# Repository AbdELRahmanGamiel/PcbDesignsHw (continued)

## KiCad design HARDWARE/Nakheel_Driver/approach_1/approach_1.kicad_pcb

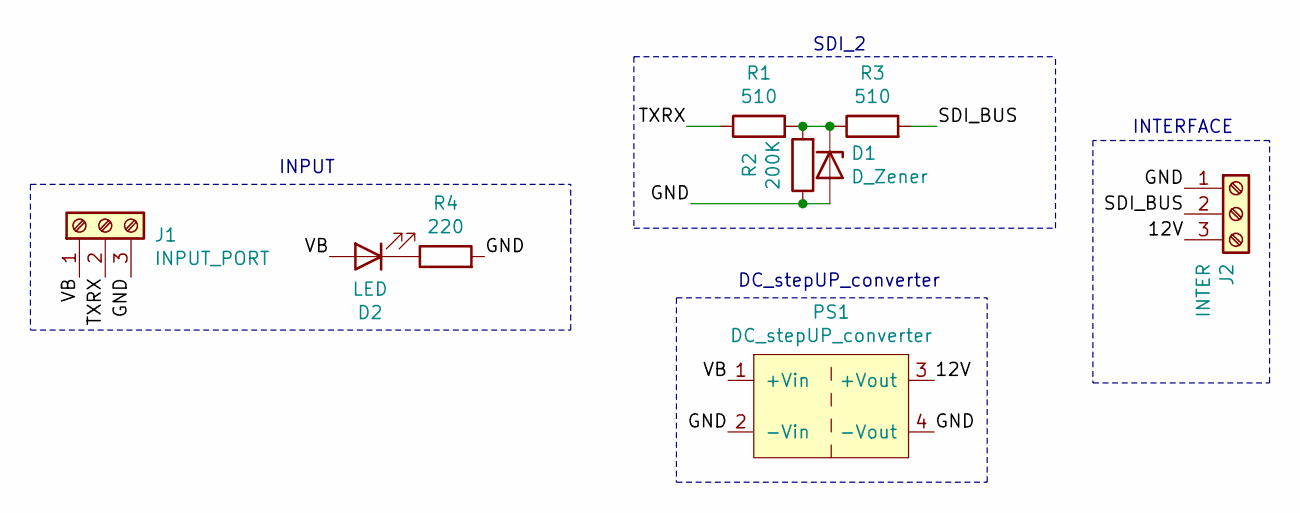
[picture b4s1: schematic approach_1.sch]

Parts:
D1: D_Zener; D_A-405_P7.62mm_Horizontal
D2: LED; LED_D5.0mm
J1: INPUT_PORT; PhoenixContact_MSTBA_2,5_3-G-5,08_1x03_P5.08mm_Horizontal
J2: INTER; PhoenixContact_MSTBA_2,5_3-G-5,08_1x03_P5.08mm_Horizontal
PS1: DC_stepUP_converter
R1, R3: 510; R_Axial_DIN0207_L6.3mm_D2.5mm_P10.16mm_Horizontal
R2: 200K; R_Axial_DIN0207_L6.3mm_D2.5mm_P10.16mm_Horizontal
R4: 220; R_Axial_DIN0207_L6.3mm_D2.5mm_P10.16mm_Horizontal

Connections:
/12V: J2.3, PS1.3 (+Vout)
/GND: D1.2 (A), J1.3, J2.1, PS1.2 (-Vin), PS1.4 (-Vout), R2.1, R4.2
/SDI_BUS: J2.2, R3.2
/TXRX: J1.2, R1.1
/VB: D2.2 (A), J1.1, PS1.1 (+Vin)
unnamed: D1.1 (K), R1.2, R2.2, R3.1
unnamed: D2.1 (K), R4.1

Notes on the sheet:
INPUT
DC_stepUP_converter
SDI_2
INTERFACE

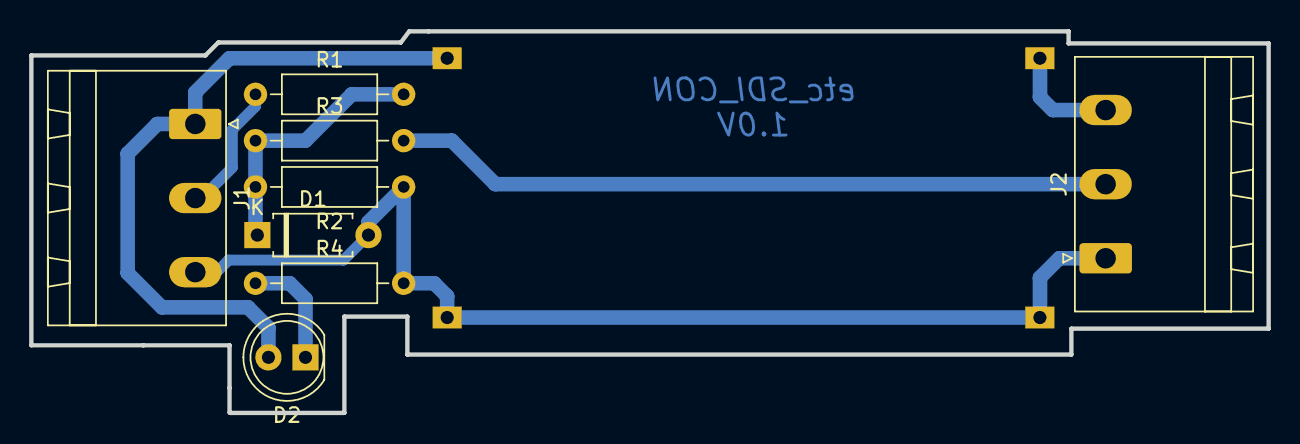
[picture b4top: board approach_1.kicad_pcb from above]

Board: 2 copper layers, 84.8 x 26.2 mm, 9 parts (0 on the bottom side), 7 nets.

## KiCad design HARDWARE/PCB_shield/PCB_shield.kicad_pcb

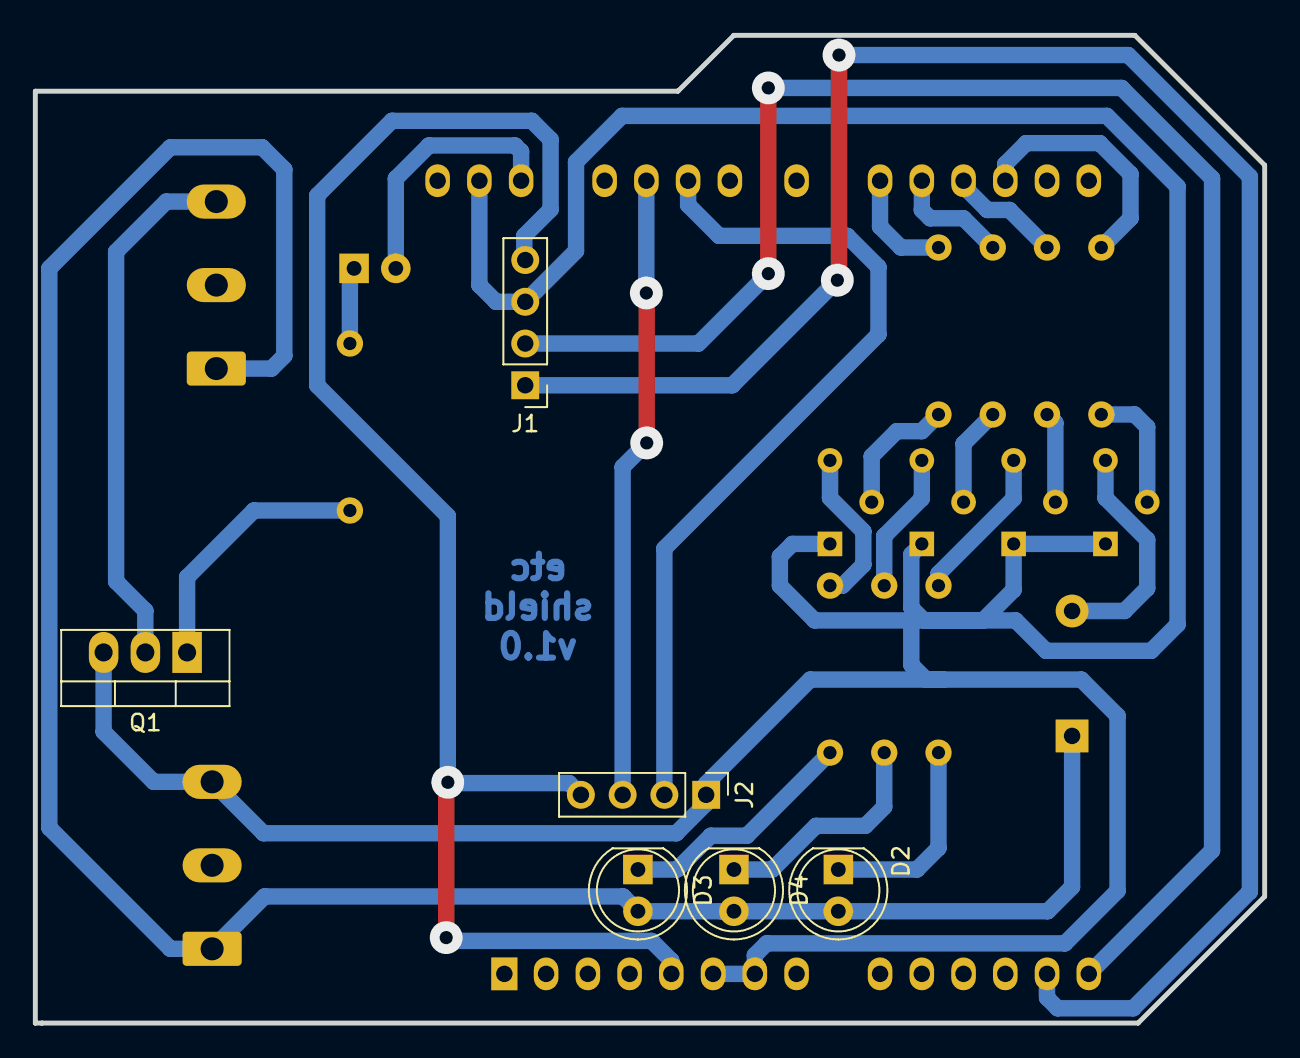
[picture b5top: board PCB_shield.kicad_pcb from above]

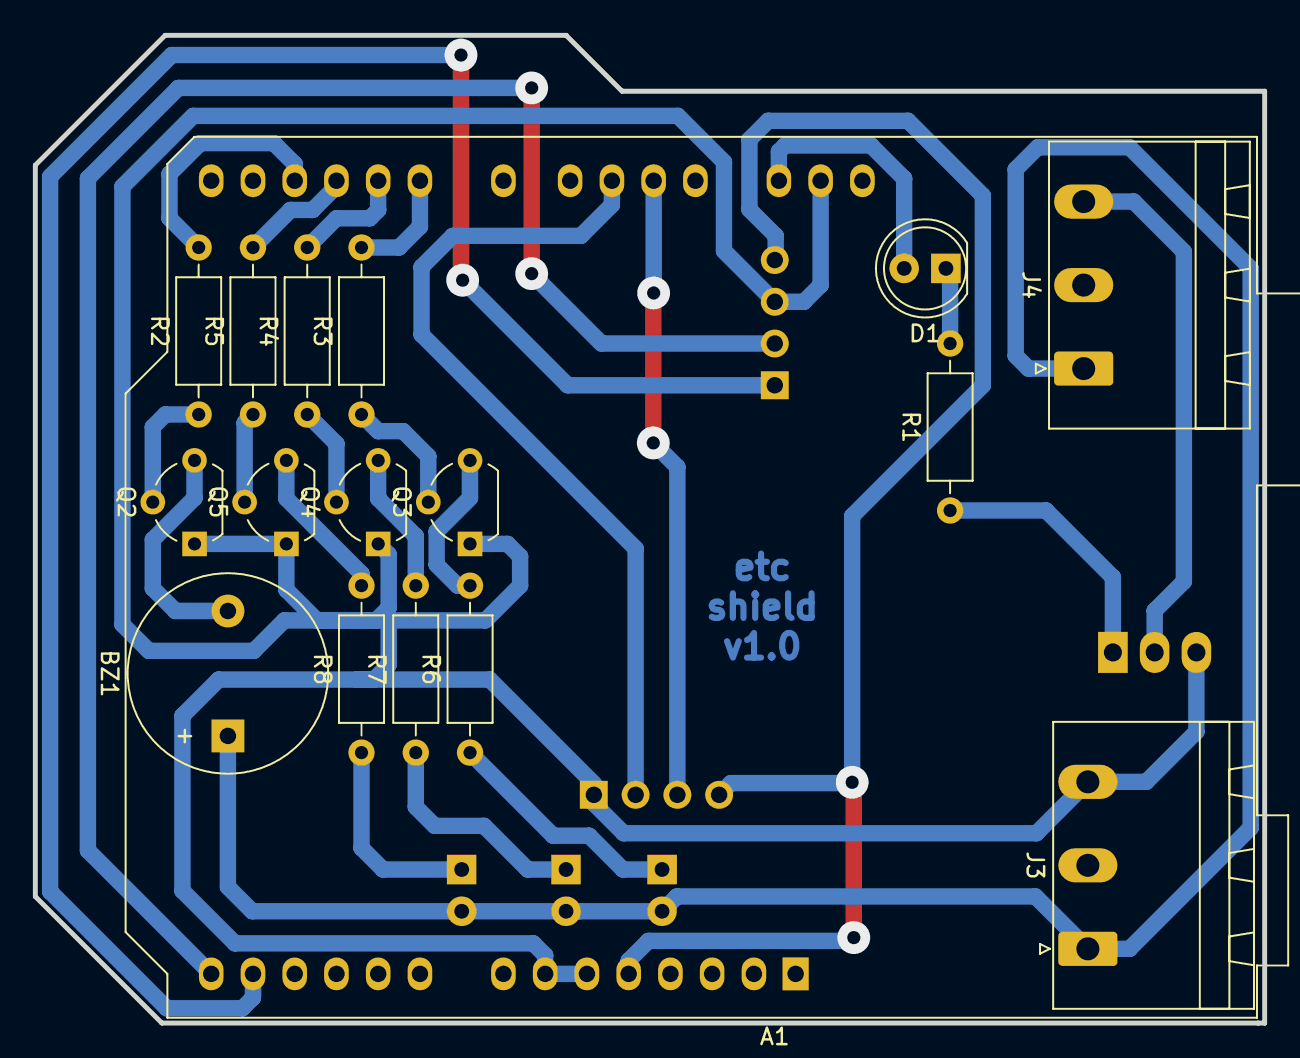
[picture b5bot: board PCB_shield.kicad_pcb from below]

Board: 2 copper layers, 74.8 x 60.1 mm, 23 parts (17 on the bottom side), 26 nets.

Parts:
A1: Arduino_UNO_R2
BZ1: Buzzer; Buzzer_12x9.5RM7.6
D1, D4: Red; LED_D5.0mm
D2: Blue; LED_D5.0mm
D3: Green; LED_D5.0mm
J1: MLX; PinHeader_1x04_P2.54mm_Vertical
J2: Ultra_sonic; PinHeader_1x04_P2.54mm_Vertical
J3, J4: pump; PhoenixContact_MSTBA_2,5_3-G-5,08_1x03_P5.08mm_Horizontal
Q1: TIP41C; TO-220-3_Vertical
Q2, Q3, Q4, Q5: 2N2219; TO-92L_Wide
R1, R2, R3, R4, R5: 1K; R_Axial_DIN0207_L6.3mm_D2.5mm_P10.16mm_Horizontal
R6, R7, R8: 470; R_Axial_DIN0207_L6.3mm_D2.5mm_P10.16mm_Horizontal

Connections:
/5V: A1.5, J1.4, J2.4
/12V: BZ1.1, D2.2, D3.2, D4.2, J3.1, J4.1
/BLUE: A1.18, R5.2
/BUZZER: A1.17, R2.2
/ECHO: A1.24, J2.2
/GND: A1.6, A1.7, A1.29, J1.3, J2.1, J3.3, Q1.3, Q2.1, Q3.1, Q4.1, Q5.1
/GREEN: A1.20, R3.2
/OUTPUT: J4.3, Q1.2
/RED: A1.19, R4.2
/SCL: A1.14, J1.2
/SDA: A1.13, J1.1
/TRIG: A1.25, J2.3
/pump: A1.28, D1.2
unnamed: BZ1.2, Q2.3
unnamed: D1.1, R1.2
unnamed: D2.1, R8.1
unnamed: D3.1, R6.1
unnamed: D4.1, R7.1
unnamed: Q1.1, R1.1
unnamed: Q2.2, R2.1
unnamed: Q3.2, R3.1
unnamed: Q3.3, R6.2
unnamed: Q4.2, R4.1
unnamed: Q4.3, R7.2
unnamed: Q5.2, R5.1
unnamed: Q5.3, R8.2

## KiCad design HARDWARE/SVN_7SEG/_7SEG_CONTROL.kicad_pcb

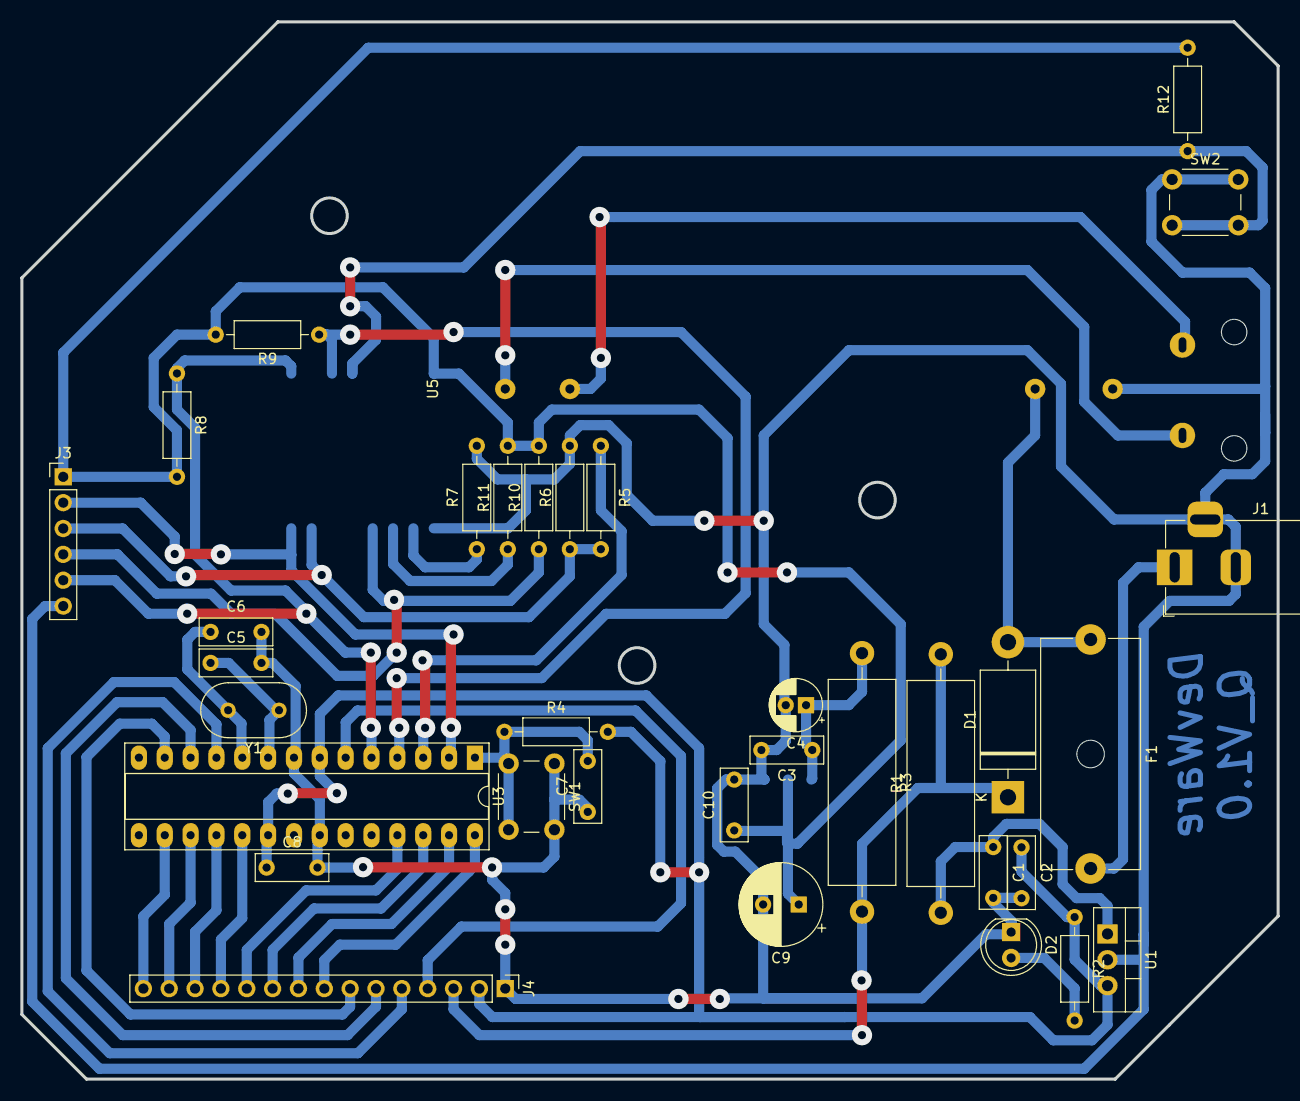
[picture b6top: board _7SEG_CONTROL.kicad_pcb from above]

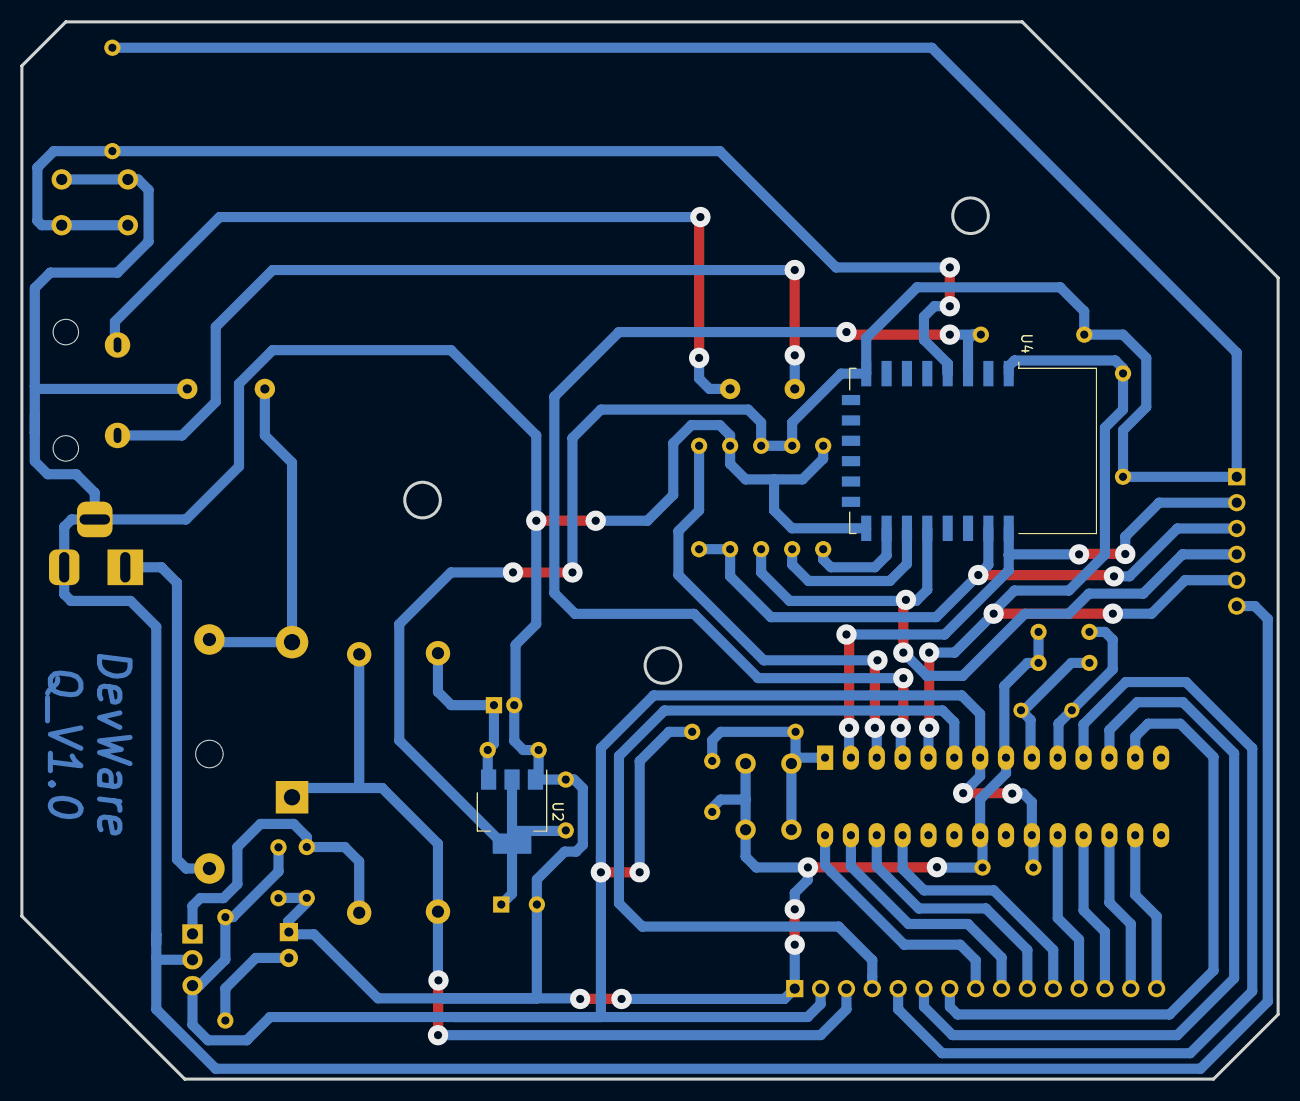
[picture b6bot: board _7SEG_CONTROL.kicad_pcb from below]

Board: 2 copper layers, 123.4 x 103.9 mm, 37 parts (2 on the bottom side), 35 nets.

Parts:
C1, C3: 334; C_Disc_D7.0mm_W2.5mm_P5.00mm
C2, C7, C10: 104; C_Disc_D7.0mm_W2.5mm_P5.00mm
C4: 10UF; CP_Radial_D5.0mm_P2.00mm
C5, C6: 22P; C_Disc_D7.0mm_W2.5mm_P5.00mm
C8: 0.1UF; C_Disc_D7.0mm_W2.5mm_P5.00mm
C9: 100UF; CP_Radial_D8.0mm_P3.50mm
D1: 1N5407; D_DO-201AD_P15.24mm_Horizontal
D2: LED; LED_D5.0mm
F1: Fuse; Fuseholder_Cylinder-5x20mm_Schurter_0031_8201_Horizontal_Op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
J1: Barrel_Jack_Switch; BarrelJack_Horizontal
J2: AC_Socket
J3: CONFIG_ESP12; PinHeader_1x06_P2.54mm_Vertical
J4: Display_Board; PinHeader_1x15_P2.54mm_Vertical
R1: 10/2W; R_Axial_Power_L20.0mm_W6.4mm_P25.40mm
R2: 330; R_Axial_DIN0207_L6.3mm_D2.5mm_P10.16mm_Horizontal
R3: 10/3W; R_Axial_Power_L20.0mm_W6.4mm_P25.40mm
R4, R5, R6, R12: 10K; R_Axial_DIN0207_L6.3mm_D2.5mm_P10.16mm_Horizontal
R7, R8, R9, R10, R11: 12K; R_Axial_DIN0207_L6.3mm_D2.5mm_P10.16mm_Horizontal
SW1, SW2: SW_Push; SW_PUSH_6mm_H7.3mm
U1: L7805; TO-220-3_Vertical
U2: AMS1117-3.3; SOT-223-3_TabPin2
U3: ATmega328-PU; DIP-28_W7.62mm_Socket_LongPads
U4: ESP-12E
U5: PS-12VDC; PS_12VDC
Y1: 16MH; Resonator-2Pin_W10.0mm_H5.0mm

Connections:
/3.3V: C9.1, C10.1, J3.1, R8.2, R9.2, R10.2, R11.2, R12.2, U2.2, U4.8
/5V: C2.1, C8.1, J4.2, R2.1, R4.2, U1.3, U3.7, U3.20
/12V: D1.1, J4.3, R1.2, R3.2
/A_D1: J4.15, U3.16
/A_D2: J4.11, U3.25
/A_D3: J4.7, U3.13
/B_D1: J4.12, U3.19
/B_D2: J4.8, U3.28
/B_D3: J4.4, U3.6
/C_D1: J4.13, U3.18
/C_D2: J4.9, U3.27
/C_D3: J4.5, U3.11
/D_D1: J4.14, U3.17
/D_D2: J4.10, U3.26
/D_D3: J4.6, U3.12
/EN: R9.1, U3.4, U4.3
/GND: C1.2, C2.2, C3.2, C4.2, C5.2, C6.2, C7.1, C8.2, C9.2, C10.2, D2.1, J1.2, J1.3, J3.6, J4.1, R6.2, R7.2, SW1.1, SW2.1, U1.2, U2.1, U3.8, U3.22, U4.15, U5.4
/IO0: J3.4, R10.1, U4.18
/IO2: R11.1, U4.17
/IO15: R7.1, U4.16
/Interrupt: R12.1, SW2.2, U4.4
/RST: J3.5, R8.1, U3.5, U4.1
/RX-MCU: J3.2, U3.2, U4.22
/RXD: J3.3, R5.2, R6.1, U4.21
/TX_MCU: R5.1, U3.3
/V+: D1.2, F1.1, U5.3
unnamed: C1.1, R1.1, U1.1
unnamed: C3.1, C4.1, R3.1, U2.3
unnamed: C5.1, U3.9, Y1.1
unnamed: C6.1, U3.10, Y1.2
unnamed: C7.2, R4.1, SW1.2, U3.1
unnamed: D2.2, R2.2
unnamed: F1.2, J1.1
unnamed: J2.L, U5.1
unnamed: J2.N, U5.2

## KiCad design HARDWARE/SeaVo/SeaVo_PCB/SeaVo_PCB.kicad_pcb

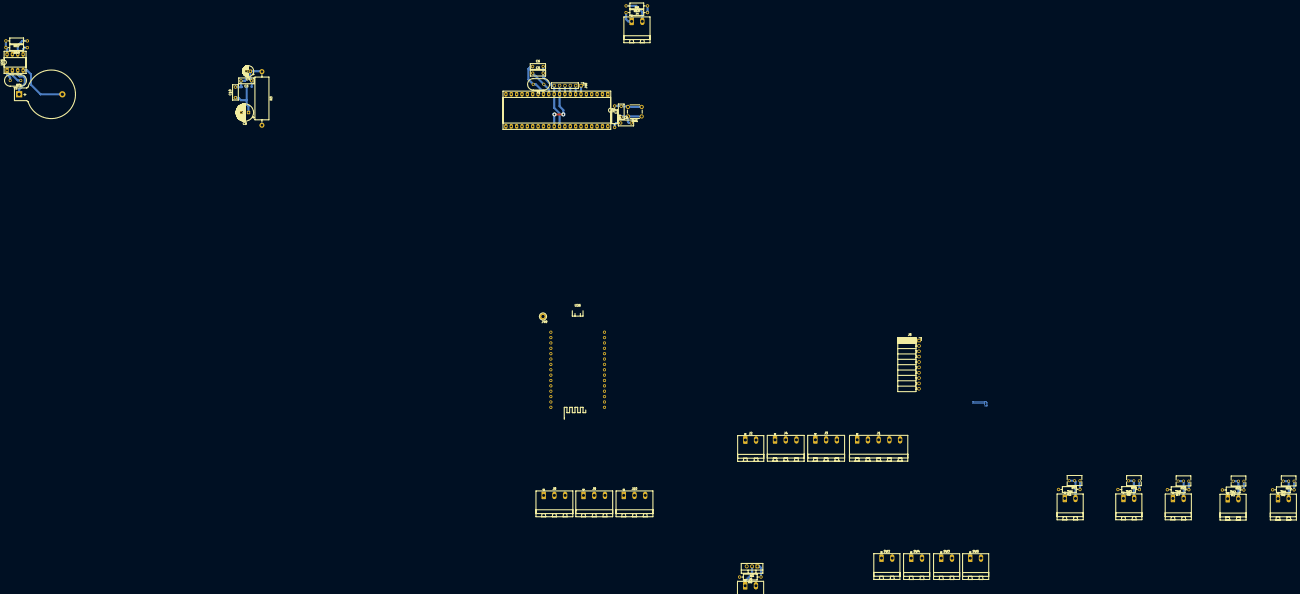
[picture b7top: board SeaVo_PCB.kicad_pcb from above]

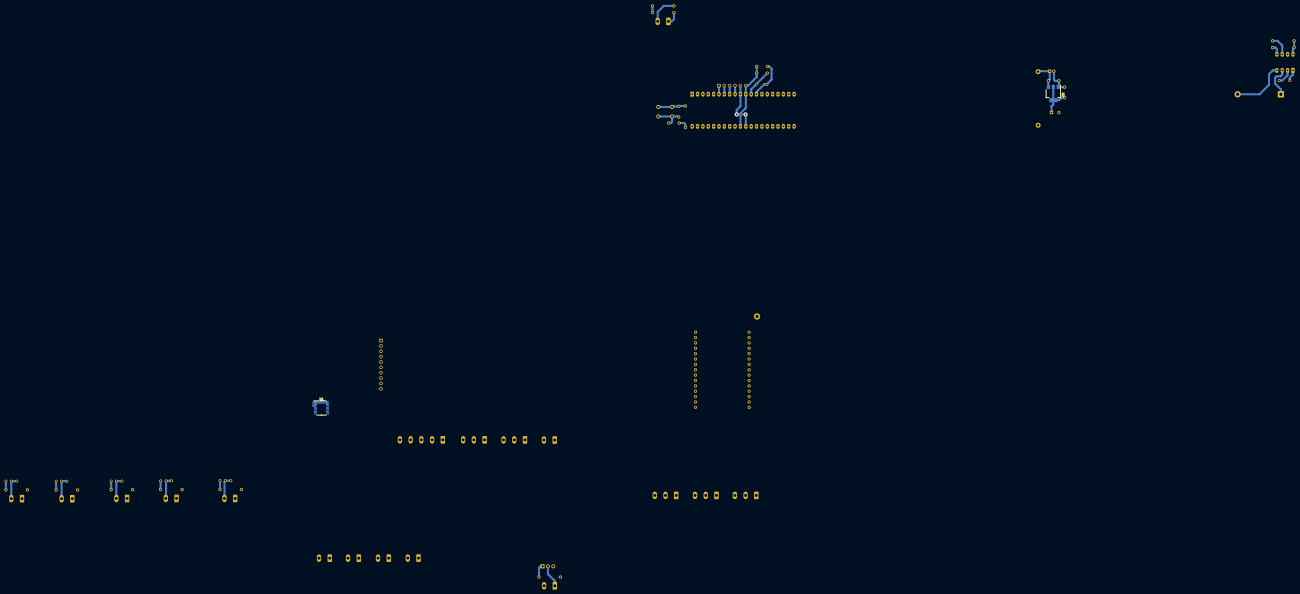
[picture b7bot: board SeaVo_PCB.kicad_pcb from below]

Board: 2 copper layers, 56 parts (2 on the bottom side), 51 nets.

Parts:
BT1: Battery_Cell; BatteryHolder_Keystone_103_1x20mm
C3: 334; C_Disc_D7.0mm_W2.5mm_P5.00mm
C4: 10UF; CP_Radial_D5.0mm_P2.00mm
C5, C6: 22P; C_Disc_D7.0mm_W2.5mm_P5.00mm
C7, C10: 104; C_Disc_D7.0mm_W2.5mm_P5.00mm
C8: 0.1UF; C_Disc_D7.0mm_W2.5mm_P5.00mm
C9: 100UF; CP_Radial_D8.0mm_P3.50mm
J1: LCD; PhoenixContact_MSTBA_2,5_5-G-5,08_1x05_P5.08mm_Horizontal
J2: BMS; PhoenixContact_MSTBA_2,5_2-G-5,08_1x02_P5.08mm_Horizontal
J3: ESC1; PhoenixContact_MSTBA_2,5_3-G-5,08_1x03_P5.08mm_Horizontal
J4: ESC2; PhoenixContact_MSTBA_2,5_3-G-5,08_1x03_P5.08mm_Horizontal
J5: ADC_Module; PinSocket_1x10_P2.54mm_Horizontal
J6: PUMP; PhoenixContact_MSTBA_2,5_2-G-5,08_1x02_P5.08mm_Horizontal
J7: Battery; PhoenixContact_MSTBA_2,5_2-G-5,08_1x02_P5.08mm_Horizontal
J8: Current_BMS; PhoenixContact_MSTBA_2,5_3-G-5,08_1x03_P5.08mm_Horizontal
J9: Current_ESC1; PhoenixContact_MSTBA_2,5_3-G-5,08_1x03_P5.08mm_Horizontal
J10: Current_ESC2; PhoenixContact_MSTBA_2,5_3-G-5,08_1x03_P5.08mm_Horizontal
J40: SPI(ISP); PinHeader_1x06_P2.54mm_Vertical
J49: BOOT_Pad; TestPoint_Loop_D2.54mm_Drill1.5mm_Beaded
Q1: TIP41; TO-220-3_Vertical
R1, R2, R5, R6, R7, R8, R10: 1K; R_Axial_DIN0207_L6.3mm_D2.5mm_P10.16mm_Horizontal
R3: 10/3W; R_Axial_Power_L20.0mm_W6.4mm_P25.40mm
R4, R57, R58: 10K; R_Axial_DIN0207_L6.3mm_D2.5mm_P10.16mm_Horizontal
R9: 19K; R_Axial_DIN0207_L6.3mm_D2.5mm_P10.16mm_Horizontal
RV1: Battery_POT; Potentiometer_Bourns_3266Y_Vertical
RV2: M1_POT; Potentiometer_Bourns_3266Y_Vertical
RV3: ESC1_POT; Potentiometer_Bourns_3266Y_Vertical
RV4: M2_POT; Potentiometer_Bourns_3266Y_Vertical
RV5: ESC2_POT; Potentiometer_Bourns_3266Y_Vertical
SW1: SW_Push; SW_PUSH_6mm_H7.3mm
SW2: P1; PhoenixContact_MSTBA_2,5_2-G-5,08_1x02_P5.08mm_Horizontal
SW3: P3; PhoenixContact_MSTBA_2,5_2-G-5,08_1x02_P5.08mm_Horizontal
SW4: P2; PhoenixContact_MSTBA_2,5_2-G-5,08_1x02_P5.08mm_Horizontal
SW5: P4; PhoenixContact_MSTBA_2,5_2-G-5,08_1x02_P5.08mm_Horizontal
TH1: Thermistor_Battery; PhoenixContact_MSTBA_2,5_2-G-5,08_1x02_P5.08mm_Horizontal
TH2: Thermistor_M1; PhoenixContact_MSTBA_2,5_2-G-5,08_1x02_P5.08mm_Horizontal
TH3: Thermistor_ESC1; PhoenixContact_MSTBA_2,5_2-G-5,08_1x02_P5.08mm_Horizontal
TH4: Thermistor_M2; PhoenixContact_MSTBA_2,5_2-G-5,08_1x02_P5.08mm_Horizontal
TH5: Thermistor_ESC2; PhoenixContact_MSTBA_2,5_2-G-5,08_1x02_P5.08mm_Horizontal
U1: ADC_MCP3461R; TSSOP-20_4.4x6.5mm_P0.65mm
U2: AMS1117-3.3; SOT-223-3_TabPin2
U3: ATmega32-16PU; DIP-40_W15.24mm_Socket_LongPads
U25: DS1307+; DIP-8_W7.62mm_Socket_LongPads
U26: ESP32_module
Y1: 16MH; Resonator-2Pin_W10.0mm_H5.0mm
Y2: Crystal; Resonator-2Pin_W10.0mm_H5.0mm

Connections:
/3.3V: C9.1, C10.1, U1.1, U1.4, U1.20, U2.2
/5V: C8.1, J1.1, J5.1, J8.1, J9.1, J10.1, J40.5, R4.2, R57.2, R58.2, TH1.1, TH2.1, TH3.1, TH4.1, TH5.1, U3.10, U3.30, U25.8, U26.16
/12V: J6.2, R3.2
/ALRT: J5.6, U3.21
/BMS_Current: J5.7, J8.2, U1.6
/BOOT: J49.1, U3.19
/Bat_Temp: RV1.1, RV1.2, TH1.2, U3.40
/EN_ESP32: U3.20, U26.30
/ESC1_Current: J9.2, U3.35
/ESC1_Temp: RV3.1, RV3.2, TH3.2, U3.39
/ESC2_Current: J10.2, U3.34
/ESC2_Temp: RV5.1, RV5.2, TH5.2, U3.38
/GND: BT1.2, C3.2, C4.2, C5.2, C6.2, C7.1, C8.2, C9.2, C10.2, J1.4, J5.2, J7.2, J8.3, J9.3, J10.3, J40.6, Q1.3, R1.2, R2.2, R5.2, R6.2, R7.2, R10.2, SW1.1, SW2.2, SW3.2, SW4.2, SW5.2, U1.2, U1.3, U1.19, U2.1, U3.11, U3.31, U25.4, U26.2, U26.17
/M1_Temp: RV2.1, RV2.2, TH2.2, U3.37
/M2_Temp: RV4.1, RV4.2, TH4.2, U3.36
/MISO: J40.2, SW5.1, U1.15, U3.7
/MOSI: J40.1, SW3.1, U1.16, U3.6
/OUT_PUMP: J6.1, Q1.2
/P1: SW2.1, U3.4
/P2: SW4.1, U3.5
/PUMP: R8.2, U3.1, U3.18
/RST: C7.2, J40.4, R4.1, SW1.2, U3.9
/RX-MCU: U3.14, U26.13
/RX_BMS: J2.2, U3.16
/RX_LCD: J1.3, U3.2
/SCK: J40.3, U1.14, U3.8
/SCL: J5.3, R57.1, U3.22, U25.6
/SDA: J5.4, R58.1, U3.23, U25.5
/TX_BMS: J2.1, U3.17
/TX_LCD: J1.2, U3.3
/TX_MCU: U3.15, U26.12
/V_Sensing: R9.2, R10.1, U3.33
/u1: J3.1, U3.26
/u2: J4.1, U3.29
/v1: J3.2, U3.25
/v2: J4.2, U3.28
/w1: J3.3, U3.24
/w2: J4.3, U3.27
unnamed: BT1.1, U25.3
unnamed: C3.1, C4.1, R3.1, U2.3
unnamed: C5.1, U3.12, Y1.1
unnamed: C6.1, U3.13, Y1.2
unnamed: J7.1, R9.1
unnamed: Q1.1, R8.1
unnamed: R1.1, RV1.3
unnamed: R2.1, RV2.3
unnamed: R5.1, RV3.3
unnamed: R6.1, RV4.3
unnamed: R7.1, RV5.3
unnamed: U25.1, Y2.2
unnamed: U25.2, Y2.1
